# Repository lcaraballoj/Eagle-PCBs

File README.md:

# Eagle-PCBs
This is a collection of some Eagle PCB designs that I created during my time working at the [Sacred Heart University IDEA Lab](https://www.sacredheart.edu/academics/colleges--schools/school-of-computer-science--engineering/facilities/idea-lab/).

## <a href="https://github.com/lcaraballoj/Arduino-Gamepad" target="_blank">Gamepad</a>
The Gamepad PCB is a PCB that was created for a USB gamepad powered by an Arduino Pro Micro. The PCB was utilized in a workshop in which participants could learn to through-hole solder using the custom PCBs.

**Buttons**

**Main Body**

## Pumpkin PCB
This was a PCB that was created for a workshop in which users learned to through-hold solder by soldering LEDs arranged to create a Jack O'Latern. 

## SHUduino
This was a challenging PCB that was created with the intention of being used by the engineering students in order to teach them surface-mount soldering and to teach them to encode an Arduino. This PCB did not end up working, and there was not enough time to troublehsoot and the issues, but a lot of work was put into it and it ended up looking cool despite it not being functional. 

## Snowflake
This was a PCB that was created in order to test out making our own PCBs in the IDEA Lab. We did this by using the the [Carvey](https://site.inventables.com/press/materials/carvey) by Inventables and copper plates in which we used the Carvey to carve the outline of our circuit. 

(The SHU on the ends were added after testing on the Carvey)

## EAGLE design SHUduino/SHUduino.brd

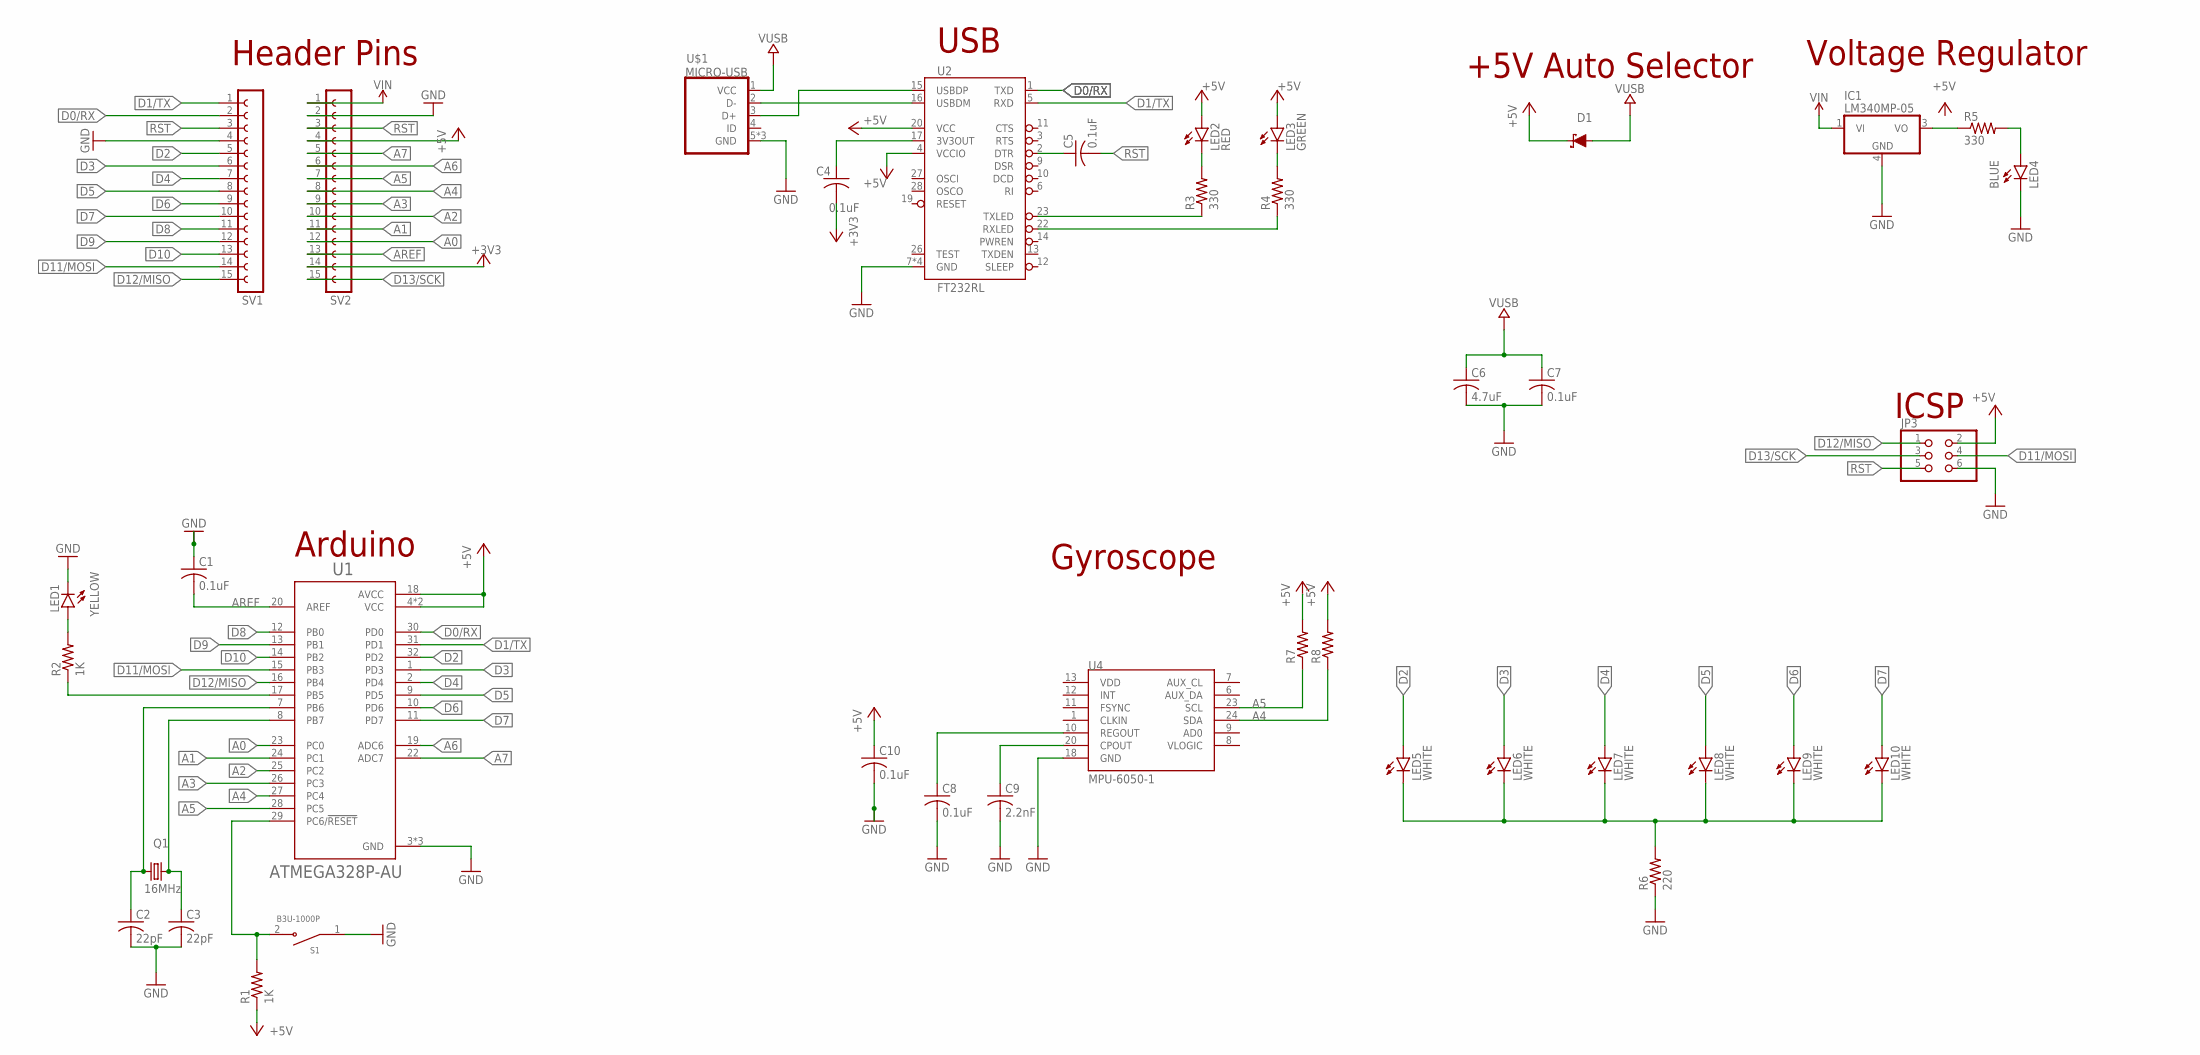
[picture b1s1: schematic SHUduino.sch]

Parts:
C1, C4, C5, C7, C8, C10: 0.1uF; C3225
C2, C3: 22pF; C3225
C6: 4.7uF; C3225
C9: 2.2nF; C3225
D1: 0.5A 20V; SOD-323
IC1: LM340MP-05; SOT223
JP3: PINHD-2X3; 2X03
LED1: YELLOW; SML0603
LED2: RED; SML0603
LED3: GREEN; SML0603
LED4: BLUE; SML0603
LED5, LED6, LED7, LED8, LED9, LED10: WHITE; SML0603
Q1: 16MHz; HC49/S
R1, R2: 1K; M1206
R3, R4, R5: 330; M1206
R6: 220; M1206
R7, R8: R-US_M1206; M1206
S1: B3U-1000P; SW_B3U-1000P
SV1, SV2: FE15-1; FE15
U1: ATMEGA328P-AU; QFP80P900X900X120-32N
U2: FT232RL; SSOP28DB
U4: MPU-6050-1; QFN-24-4MM2
U$1: MICRO-USB

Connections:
+3V3: C4.2, SV2.14
+5V: C10.1, D1.C, JP3.2, LED2.A, LED3.A, R1.1, R7.2, R8.2, SV2.4, U1.4 (VCC), U1.6 (VCC), U1.18 (AVCC), U2.4 (VCCIO), U2.20 (VCC)
A0: SV2.12, U1.23 (PC0)
A1: SV2.11, U1.24 (PC1)
A2: SV2.10, U1.25 (PC2)
A3: SV2.9, U1.26 (PC3)
A4: R8.1, SV2.8, U1.27 (PC4), U4.24 (SDA)
A5: R7.1, SV2.7, U1.28 (PC5), U4.23 (SCL)
A6: SV2.6, U1.19 (ADC6)
A7: SV2.5, U1.22 (ADC7)
AREF: C1.2, SV2.13, U1.20 (AREF)
D0/RX: SV1.2, U1.30 (PD0), U2.1 (TXD)
D1/TX: SV1.1, U1.31 (PD1), U2.5 (RXD)
D2: LED5.A, SV1.5, U1.32 (PD2)
D3: LED6.A, SV1.6, U1.1 (PD3)
D4: LED7.A, SV1.7, U1.2 (PD4)
D5: LED8.A, SV1.8, U1.9 (PD5)
D6: LED9.A, SV1.9, U1.10 (PD6)
D7: LED10.A, SV1.10, U1.11 (PD7)
D8: SV1.11, U1.12 (PB0)
D9: SV1.12, U1.13 (PB1)
D10: SV1.13, U1.14 (PB2)
D11/MOSI: JP3.4, SV1.14, U1.15 (PB3)
D12/MISO: JP3.1, SV1.15, U1.16 (PB4)
D13/SCK: JP3.3, SV2.15
GND: C1.1, C2.2, C3.2, C6.2, C7.2, C8.2, C9.2, C10.2, IC1.4 (GND), JP3.6, LED1.C, LED4.C, R6.1, SV1.4, SV2.2, U1.3 (GND), U1.5 (GND), U1.21 (GND), U2.7 (GND), U2.18 (GND), U2.21 (GND), U2.25 (GND), U4.18 (GND)
unnamed: C2.1, Q1.2, U1.7 (PB6)
unnamed: R2.1, U1.17 (PB5)
unnamed: LED1.A, R2.2
unnamed: R3.1, U2.23 (TXLED)
unnamed: R4.1, U2.22 (RXLED)
unnamed: U2.16 (USBDM), U$1.2 (D-)
unnamed: U2.15 (USBDP), U$1.3 (D+)
unnamed: LED2.C, R3.2
unnamed: C4.1, U2.17 (3V3OUT)
unnamed: LED3.C, R4.2
unnamed: C5.1, U2.2 (DTR)
unnamed: LED4.A, R5.2
unnamed: C3.1, Q1.1, U1.8 (PB7)
unnamed: U$1.5 (GND), U$1.GND1 (GND), U$1.GND2 (GND)
unnamed: IC1.3 (VO), R5.1
unnamed: LED5.C, LED6.C, LED7.C, LED8.C, LED9.C, LED10.C, R6.2
unnamed: C8.1, U4.10 (REGOUT)
unnamed: C9.1, U4.20 (CPOUT)
RST: C5.2, JP3.5, R1.2, S1.2, SV1.3, SV2.3, U1.29 (PC6/!RESET)
VIN: IC1.1 (VI), SV2.1
VUSB: C6.1, C7.1, D1.A, U$1.1 (VCC)

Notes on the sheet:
Header Pins
Arduino
ICSP
Voltage Regulator
USB
+5V Auto Selector
Gyroscope

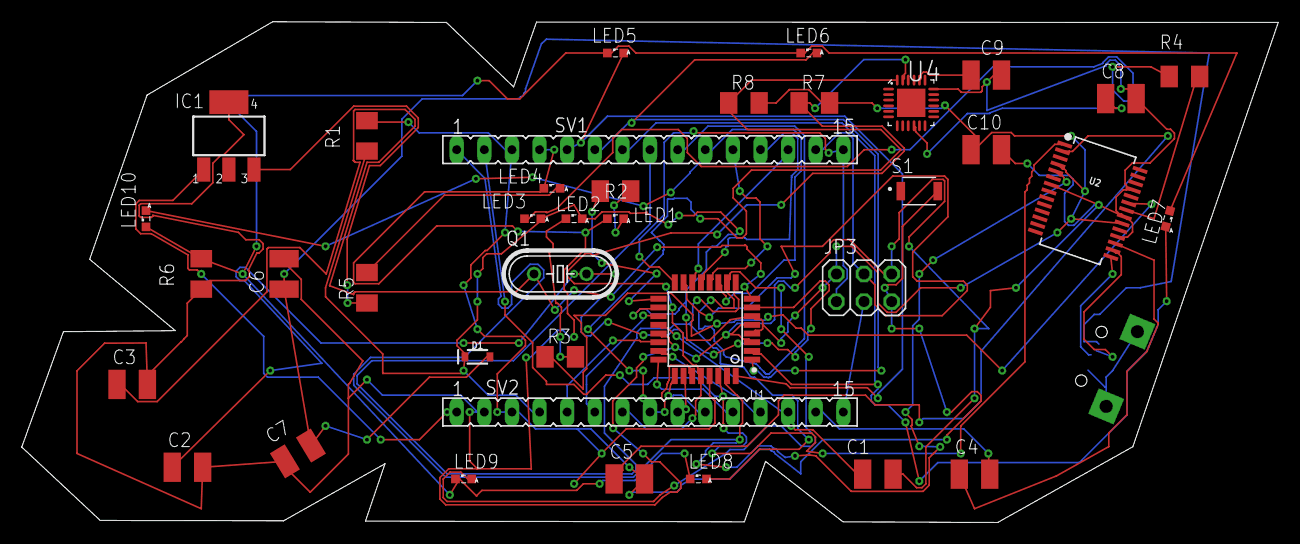
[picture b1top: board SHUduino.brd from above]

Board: 2 copper layers, 115.6 x 46.1 mm, 39 parts (1 on the bottom side), 47 nets.

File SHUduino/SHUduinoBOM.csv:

Qty,Value,Device,Package,Parts,Description,AVAILABILITY,DESCRIPTION,DIGI-KEY_PART_NUMBER,MF,MP,MPN,OC_FARNELL,OC_NEWARK,PACKAGE,POPULARITY,PRICE,PROD_ID,PURCHASE-URL,SPICEPREFIX,VALUE,
2,,FE15-1,FE15,"SV1, SV2",FEMALE HEADER,,,2041-1X16G00SA,,,,unknown,unknown,,2,,,,,,
1,,PINHD-2X3,2X03,JP3,PIN HEADER,,,A128860-ND,,,,,,,62,,,,,,
2,,R-US_M1206,M1206,"R7, R8","RESISTOR, American symbol",,,,,,,,,,22,,,,R,,
6,0.1uF,C-USC3225,C3225,"C1, C4, C5, C7, C8, C10","CAPACITOR, American symbol",,,,,,,,,,0,,,,C,,
1,0.5A 20V,DIODE-SCHOTTKY-BAT20J,SOD-323,D1,Schottky diode,,,,,,,,,,,,DIO-11623,,,1A/23V/620mV,
1,16MHz,CRYSTALHC49S,HC49/S,Q1,CRYSTAL,,,,,,,1667008,unknown,,49,,,,,,
2,1K,R-US_M1206,M1206,"R1, R2","RESISTOR, American symbol",,,,,,,,,,22,,,,R,,
1,2.2nF,C-USC3225,C3225,C9,"CAPACITOR, American symbol",,,,,,,,,,0,,,,C,,
1,220,R-US_M1206,M1206,R6,"RESISTOR, American symbol",,,,,,,,,,22,,,,R,,
2,22pF,C-USC3225,C3225,"C2, C3","CAPACITOR, American symbol",,,,,,,,,,0,,,,C,,
3,330,R-US_M1206,M1206,"R3, R4, R5","RESISTOR, American symbol",,,,,,,,,,22,,,,R,,
1,4.7uF,C-USC3225,C3225,C6,"CAPACITOR, American symbol",,,,,,,,,,0,,,,C,,
1,ATMEGA328P-AU,ATMEGA328P-AU,QFP80P900X900X120-32N,U1,ATmega Series 20 MHz 32 KB Flash 2 KB SRAM 8-Bit Microcontroller - TQFP-32 Check prices,In Stock,AVR AVR® ATmega Microcontroller IC 8-Bit 20MHz 32KB (16K x 16) FLASH 32-TQFP (7x7),,Microchip Technology,ATMEGA328P-AU,,,,TQFP-32 Microchip,,None,,https://pricing.snapeda.com/search/part/ATMEGA328P-AU/?ref=eda,,,
1,B3U-1000P,B3U-1000P,SW_B3U-1000P,S1,Switch Tactile N.O. SPST Round Button Gull Wing 0.05A 12VDC 1.5N SMD Embossed T/R,, Tactile Switch SPST-NO Top Actuated Surface Mount ,SW1020TR-ND,Omron,B3U-1000P,,,,Custom Package Omron,,,,https://pricing.snapeda.com/search/part/B3U-1000P/?ref=eda,,,
1,BLUE,LEDSML0603,SML0603,LED4,LED,,,,,,,,,,17,,,,,,
1,FT232RL,FT232RLSSOP,SSOP28DB,U2,FT232RL USB UART,,,,,,,,,,,,IC-00870,,,FT232RL,
1,GREEN,LEDSML0603,SML0603,LED3,LED,,,,,,,,,,17,,,,,,
1,LM340MP-05,LM340MP-05,SOT223,IC1,Positive VOLTAGE REGULATOR,,,,,,,,,,0,,,,,,
1,MICRO-USB,MICRO-USB,MICRO-USB,U$1,Micro USB B connector,,,,,,,,,,,,,,,,
1,MPU-6050-1,MPU-6050-1,QFN-24-4MM2,U4,,,,1428-1007-2-ND,,,,,,,,,,,,,
1,RED,LEDSML0603,SML0603,LED2,LED,,,,,,,,,,17,,,,,,
6,WHITE,LEDSML0603,SML0603,"LED5, LED6, LED7, LED8, LED9, LED10",LED,,,,,,,,,,17,,,,,,
1,YELLOW,LEDSML0603,SML0603,LED1,LED,,,,,,,,,,17,,,,,,

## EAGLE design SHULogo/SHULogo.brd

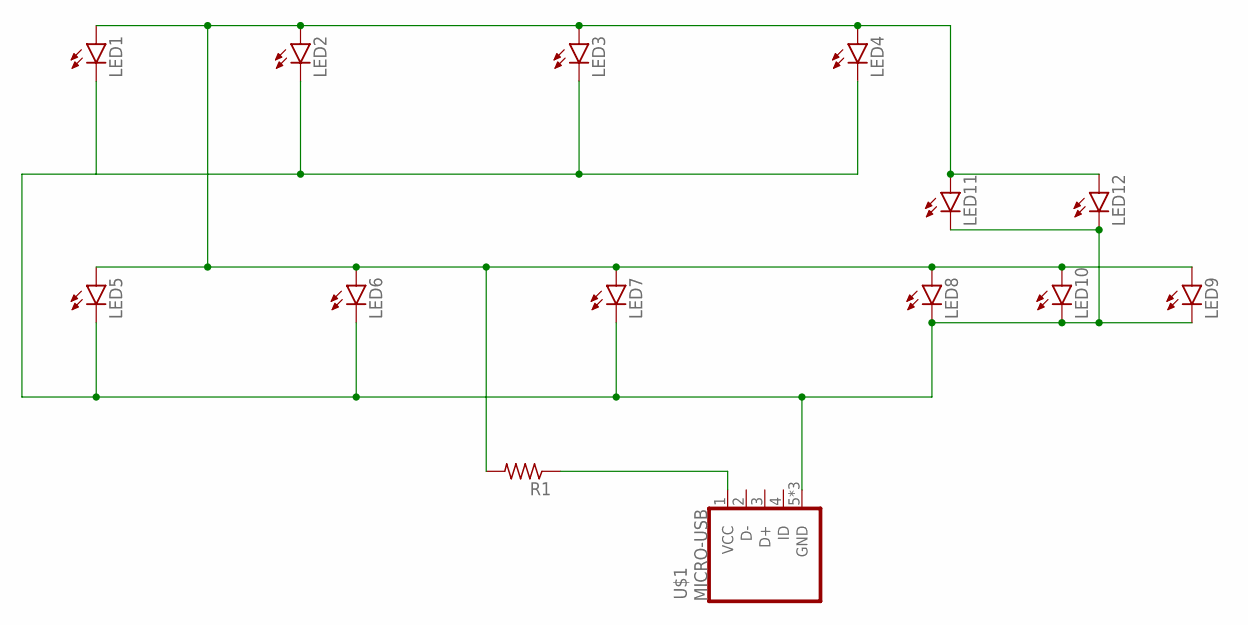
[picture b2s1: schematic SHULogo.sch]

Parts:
LED1, LED2, LED3, LED4, LED5, LED6, LED7, LED8, LED9, LED10, LED11, LED12: LED3MM
R1: R-US_M1206; M1206
U$1: MICRO-USB

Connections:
unnamed: R1.1, U$1.1 (VCC)
unnamed: LED1.A, LED2.A, LED3.A, LED4.A, LED5.A, LED6.A, LED7.A, LED8.A, LED9.A, LED10.A, LED11.A, LED12.A, R1.2
unnamed: LED1.K (C), LED2.K (C), LED3.K (C), LED4.K (C), LED5.K (C), LED6.K (C), LED7.K (C), LED8.K (C), LED9.K (C), LED10.K (C), LED11.K (C), LED12.K (C), U$1.5 (GND), U$1.GND1 (GND), U$1.GND2 (GND)

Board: 2 copper layers, 14 parts (0 on the bottom side), 3 nets, no tracks yet.

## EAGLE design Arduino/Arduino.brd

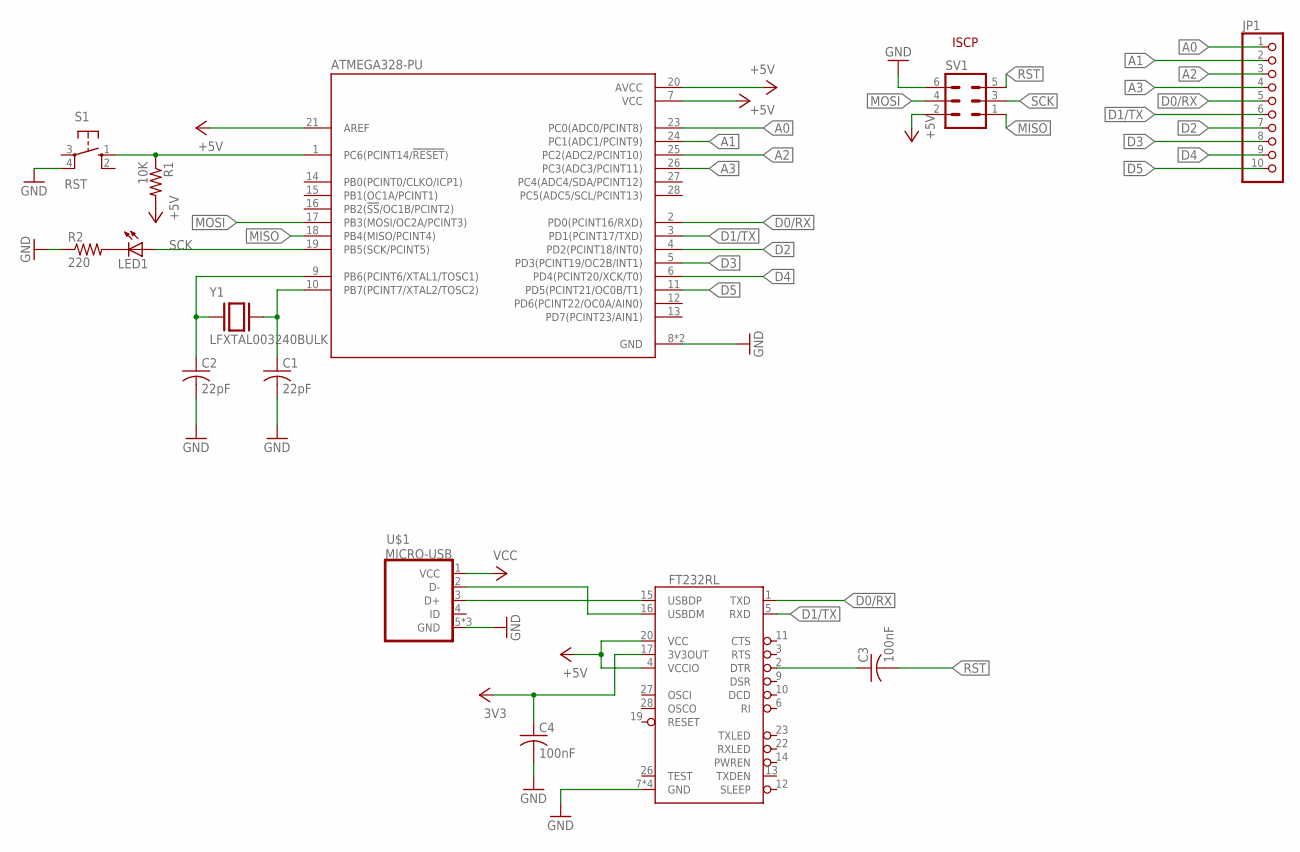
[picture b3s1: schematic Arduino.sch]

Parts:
ATMEGA328-PU: ATMEGA328-PU; DIP787W46P254L3467H508Q28
C1, C2: 22pF; C050-024X044
C3, C4: 100nF; C050-024X044
FT232RL: FT232RL; SSOP28DB
JP1: PINHD-1X10; 1X10
LED1: LED3MM
R1: 10K; 0204/7
R2: 220; 0204/7
S1: RST; B3F-10XX
SV1: MA03-2
U$1: MICRO-USB
Y1: LFXTAL003240BULK; HC49P488W45L1105T470H410

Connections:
+3V3: C4.1, FT232RL.17 (3V3OUT)
+5V: ATMEGA328-PU.7 (VCC), ATMEGA328-PU.20 (AVCC), ATMEGA328-PU.21 (AREF), FT232RL.4 (VCCIO), FT232RL.20 (VCC), R1.2, SV1.2
A0: ATMEGA328-PU.23 (PC0(ADC0/PCINT8)), JP1.1
A1: ATMEGA328-PU.24 (PC1(ADC1/PCINT9)), JP1.2
A2: ATMEGA328-PU.25 (PC2(ADC2/PCINT10)), JP1.3
A3: ATMEGA328-PU.26 (PC3(ADC3/PCINT11)), JP1.4
D0/RX: ATMEGA328-PU.2 (PD0(PCINT16/RXD)), FT232RL.1 (TXD), JP1.5
D1/TX: ATMEGA328-PU.3 (PD1(PCINT17/TXD)), FT232RL.5 (RXD), JP1.6
D2: ATMEGA328-PU.4 (PD2(PCINT18/INT0)), JP1.7
D3: ATMEGA328-PU.5 (PD3(PCINT19/OC2B/INT1)), JP1.8
D4: ATMEGA328-PU.6 (PD4(PCINT20/XCK/T0)), JP1.9
D5: ATMEGA328-PU.11 (PD5(PCINT21/OC0B/T1)), JP1.10
GND: ATMEGA328-PU.8 (GND), ATMEGA328-PU.22 (GND), C1.2, C2.2, C4.2, R2.1, S1.4 (P1), SV1.6, U$1.5 (GND), U$1.GND1 (GND), U$1.GND2 (GND)
MISO: ATMEGA328-PU.18 (PB4(MISO/PCINT4)), SV1.1
MOSI: ATMEGA328-PU.17 (PB3(MOSI/OC2A/PCINT3)), SV1.4
unnamed: ATMEGA328-PU.1 (PC6(PCINT14/!RESET!)), R1.1, S1.1 (S)
unnamed: ATMEGA328-PU.9 (PB6(PCINT6/XTAL1/TOSC1)), C2.1, Y1.1
unnamed: FT232RL.15 (USBDP), U$1.3 (D+)
unnamed: FT232RL.16 (USBDM), U$1.2 (D-)
unnamed: LED1.K (C), R2.2
unnamed: ATMEGA328-PU.10 (PB7(PCINT7/XTAL2/TOSC2)), C1.1, Y1.2
unnamed: FT232RL.7 (GND), FT232RL.18 (GND), FT232RL.21 (GND), FT232RL.25 (GND)
unnamed: C3.1, FT232RL.2 (DTR)
RST: C3.2, SV1.5
SCK: ATMEGA328-PU.19 (PB5(SCK/PCINT5)), LED1.A, SV1.3
VCC: U$1.1 (VCC)

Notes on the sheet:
ISCP

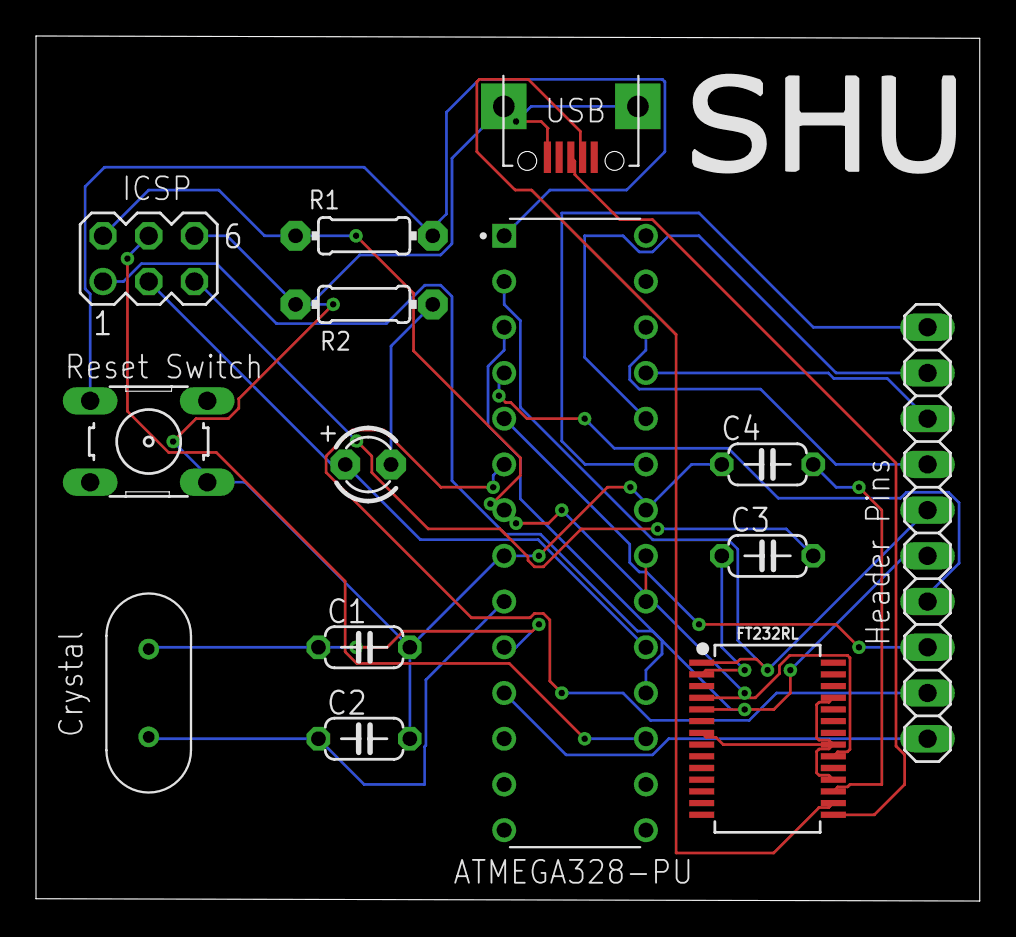
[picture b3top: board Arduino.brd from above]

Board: 2 copper layers, 52.4 x 48.1 mm, 14 parts (0 on the bottom side), 25 nets.

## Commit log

2022-06-25 Uploadding Files

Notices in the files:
parts and their libraries:
SparkFun-IC-Comms: Licensing: Creative Commons ShareAlike 4.0 International - https://creativecommons.org/licenses/by-sa/4.0
